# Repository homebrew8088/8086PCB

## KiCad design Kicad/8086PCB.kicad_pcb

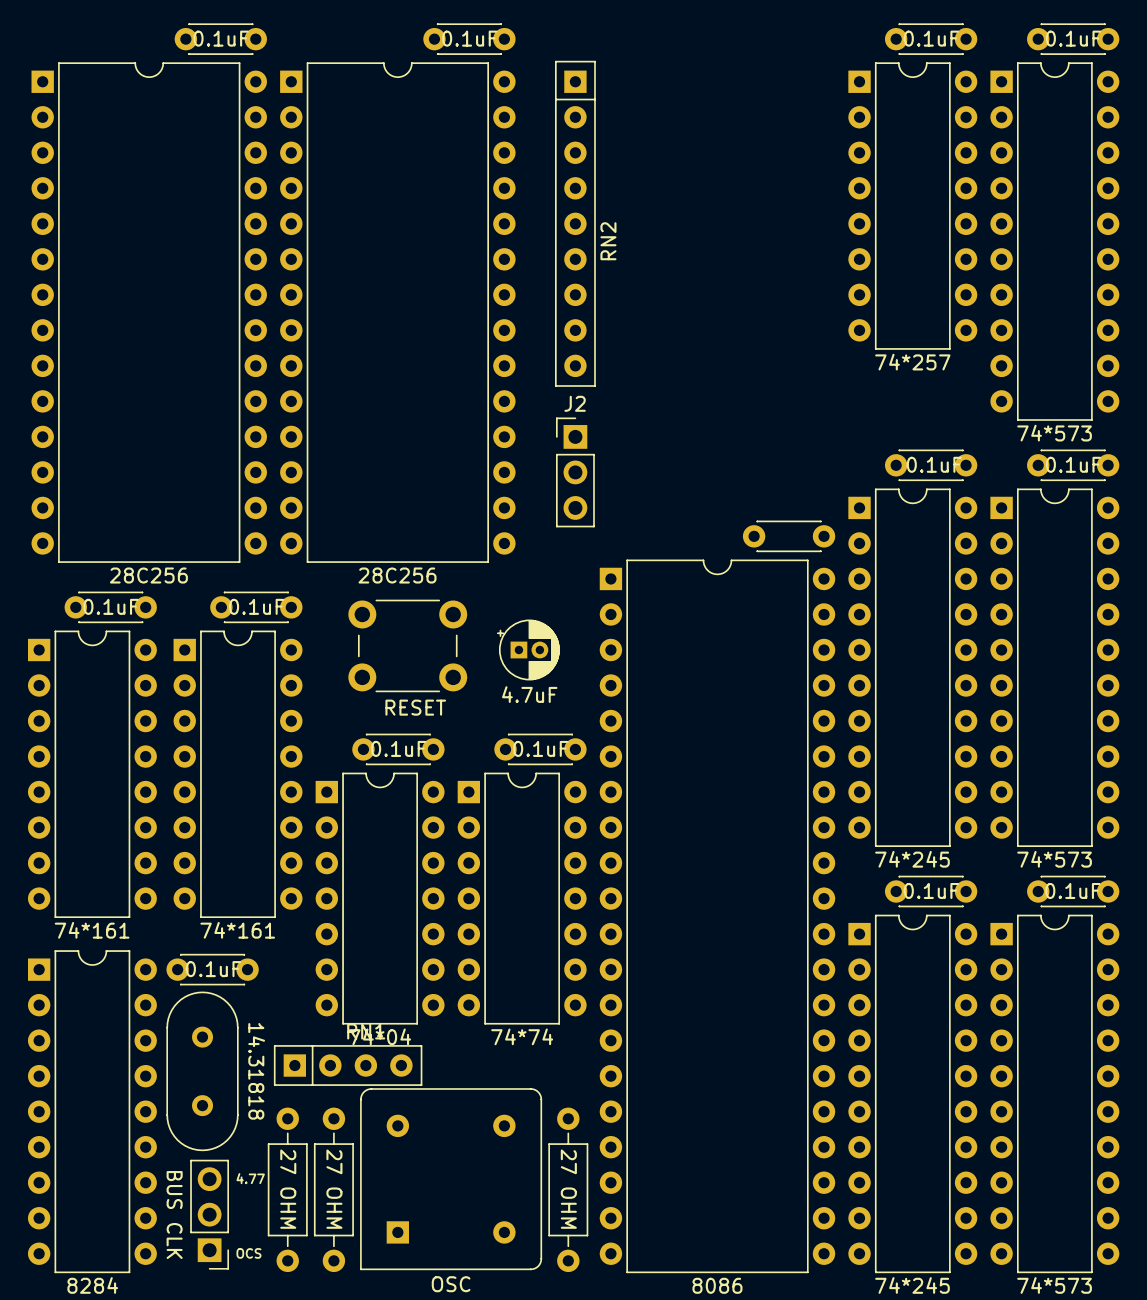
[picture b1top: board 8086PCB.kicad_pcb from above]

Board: 2 copper layers, 39 parts (0 on the bottom side), 62 nets, no tracks yet.

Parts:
C1, C2, C3, C4, C5, C6, C7, C8, C9, C10, C11, C12, C13, C14: 0.1uF; C_Disc_D4.3mm_W1.9mm_P5.00mm
C47: 4.7uF; CP_Radial_D4.0mm_P1.50mm
J1: BUS CLK; PinHeader_1x03_P2.54mm_Vertical
J2: BUS STOP; PinHeader_1x03_P2.54mm_Vertical
R1, R2, R3: 27 OHM; R_Axial_DIN0207_L6.3mm_D2.5mm_P10.16mm_Horizontal
RN1: 10K OHM; R_Array_SIP4
RN2: 10K OHM; R_Array_SIP9
SW1: RESET; SW_PUSH_6mm
U1, U3: 74*161; DIP-16_W7.62mm
U2: 74*04; DIP-14_W7.62mm
U4: 74*74; DIP-14_W7.62mm
U5: 8284; DIP-18_W7.62mm
U6: 8086; DIP-40_W15.24mm
U7, U8: 74*245; DIP-20_W7.62mm
U9, U10, U11: 74*573; DIP-20_W7.62mm
U12, U13: 28C256; DIP-28_W15.24mm
U14: 74*257; DIP-16_W7.62mm
X1: OSC; Oscillator_DIP-8
Y1: 14.31818; Crystal_HC18-U_Vertical

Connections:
/5+: C1.2, C2.2, C3.2, C4.2, C5.2, C6.2, C7.2, C8.2, C9.2, C10.2, C11.2, C12.2, C13.2, C14.2, RN1.1, RN2.1, U1.7, U1.9, U1.10, U1.16, U2.14, U3.9, U3.16, U4.2, U4.4, U4.14, U5.7, U5.18, U6.33, U6.40, U7.20, U8.20, U9.20, U10.20, U11.20, U12.27, U12.28, U13.27, U13.28, U14.16, X1.8
/A0: RN2.5, U9.12, U12.21, U13.21
/A16P: U6.38, U11.2
/A17P: U6.37, U11.3
/A18P: U6.36, U11.4
/A19P: U6.35, U11.5
/AD0: RN2.8, U6.16, U7.9, U9.9
/AD1: U6.15, U7.8, U9.8
/AD2: U6.14, U7.7, U9.7
/AD3: U6.13, U7.6, U9.6
/AD4: U6.12, U7.5, U9.5
/AD5: U6.11, U7.4, U9.4
/AD6: U6.10, U7.3, U9.3
/AD7: U6.9, U7.2, U9.2
/AD8: U6.8, U8.9, U10.9
/AD9: U6.7, U8.8, U10.8
/AD10: U6.6, U8.7, U10.7
/AD11: U6.5, U8.6, U10.6
/AD12: U6.4, U8.5, U10.5
/AD13: U6.3, U8.4, U10.4
/AD14: U6.2, U8.3, U10.3
/AD15: U6.39, U8.2, U10.2
/ALE: U2.1, U6.25, U9.11, U10.11, U11.11
/ALE_: U1.1, U2.2, U3.1, U4.1
/BHE: RN2.6, U11.15, U12.23, U13.23
/BHEP: RN2.9, U6.34, U11.6
/BUS_CLK: J1.2, U3.2
/BUS_STOP: J2.2, U3.7
/CLK4.77: J1.3, R3.1
/CLK86: R1.1, U6.19
/CLK161: J1.1, R2.1
/CLK_4.77: R3.2, U5.8
/CONTROL7: J2.3, U12.19
/CONTROL_IOM: U12.12, U14.1
/CONTROL_RD: U12.15, U14.2, U14.6
/CONTROL_WR: U12.13, U14.11, U14.13
/DEN: RN2.2, U6.26, U7.19, U8.19
/DTR: RN2.4, U6.27, U7.1, U8.1, U12.25, U13.25
/GND: C1.1, C2.1, C3.1, C4.1, C5.1, C6.1, C7.1, C8.1, C9.1, C10.1, C11.1, C12.1, C13.1, C14.1, C47.1, SW1.1, U1.8, U2.7, U3.8, U4.7, U5.1, U5.3, U5.6, U5.9, U5.13, U5.15, U6.1, U6.20, U6.23, U7.10, U8.10, U9.10, U10.10, U11.10, U12.1, U12.14, U12.20, U12.22, U12.26, U13.1, U13.14, U13.20, U13.22, U13.26, U14.8, X1.4
/HOLDA: U6.30, U9.1, U10.1, U11.1, U14.15
/INTA: U6.24, U12.2, U13.2
/IOM: RN2.3, U6.28, U12.24, U13.24
/OSC_OUT: R1.2, R2.2, X1.5
/PU1: RN2.7, U14.3, U14.5, U14.10, U14.14
/Q0: U3.14, U12.10, U13.10
/Q1: U3.13, U12.9, U13.9
/Q2: U3.12, U12.8, U13.8
/Q3: U3.11, U12.7, U13.7
/Q4: U1.14, U12.6, U13.6
/Q5: U1.13, U12.5, U13.5
/Q6: U1.12, U12.4, U13.4
/Q7: U1.11, U12.3, U13.3
/RCO: U1.2, U3.15
/RDY: U3.10, U5.5
/RDY1: RN1.3, U5.4
/RDY86: U4.5, U6.22
/RDY86_: J2.1, U4.6
/RDY_PULSE: U4.3, U12.11
/RESET: U5.10, U6.21
/RESET_: C47.2, RN1.2, SW1.2, U5.11
/X1: U5.17, Y1.1
/X2: U5.16, Y1.2

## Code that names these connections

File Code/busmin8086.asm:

;;;;;;;;;;;;;;;;;;;;;;;;;;;;;;;;;;
;ReadIOPort 16 bit from 8 bit
;BHE= 0, A0=0, IOM=0, DTR=0  
;;;;;;;;;;;;;;;;;;;;;;;;;;;;;;;;;;
IORD:

END_IORD:
TIMES 0X100-(END_IORD-IORD) DB 0XFF
;;;;;;;;;;;;;;;;;;;;;;;;;;;;;;;;;;
;WriteIOPort 16 bit to 8 bit
;BHE= 0, A0=0, IOM=0, DTR=1  
;;;;;;;;;;;;;;;;;;;;;;;;;;;;;;;;;;
IOWR:

END_IOWR:
TIMES 0X100-(END_IOWR-IOWR) DB 0XFF
;;;;;;;;;;;;;;;;;;;;;;;;;;;;;;;;;;
;ReadMemory 8 BIT 16 bit from 8 bit
;BHE= 0, A0=0, IOM=1, DTR=0  
;;;;;;;;;;;;;;;;;;;;;;;;;;;;;;;;;;
MEMRD_C1:
DB 0XFE, 0XF0, 0XF0, 0XF0, 0XF1
END_MEMRD_C1:
TIMES 0X80-(END_MEMRD_C1-MEMRD_C1) DB 0XFF
MEMRD_C2:
DB 0XFF, 0XF3, 0XF7, 0X07, 0X07
END_MEMRD_C2:
TIMES 0X80-(END_MEMRD_C2-MEMRD_C2) DB 0XFF
;;;;;;;;;;;;;;;;;;;;;;;;;;;;;;;;;;
;0  1  WriteMemory 16 bit from 8 bit
;BHE= 0, A0=0, IOM=1, DTR=1  
;;;;;;;;;;;;;;;;;;;;;;;;;;;;;;;;;;
MEMWR:

END_MEMWR:
TIMES 0X100-(END_MEMWR-MEMWR) DB 0XFF
db 0x55, 0xaa

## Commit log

2024-07-22 start
2024-08-27 Update fp-info-cache
